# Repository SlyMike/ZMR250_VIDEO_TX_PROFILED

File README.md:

# ZMR250_VIDEO_TX_PROFILED
Video TX for ZMR250 frame with 12x WS2512 LEDs.
Use the board with vertical antenna for best results.

Small switch mode power supplies are available on Ebay, solder directly to under side.
LM1117 3V3 linear regulater may be used for low power applications but not recomended (25mW).
Solder bridge jumper is provided for powering TX on 5V where possible.
Place jumper across 3V3OUT and ENABLE to turn on TX module.

I hope you find this project helpful, maybe it's worth a coffee?

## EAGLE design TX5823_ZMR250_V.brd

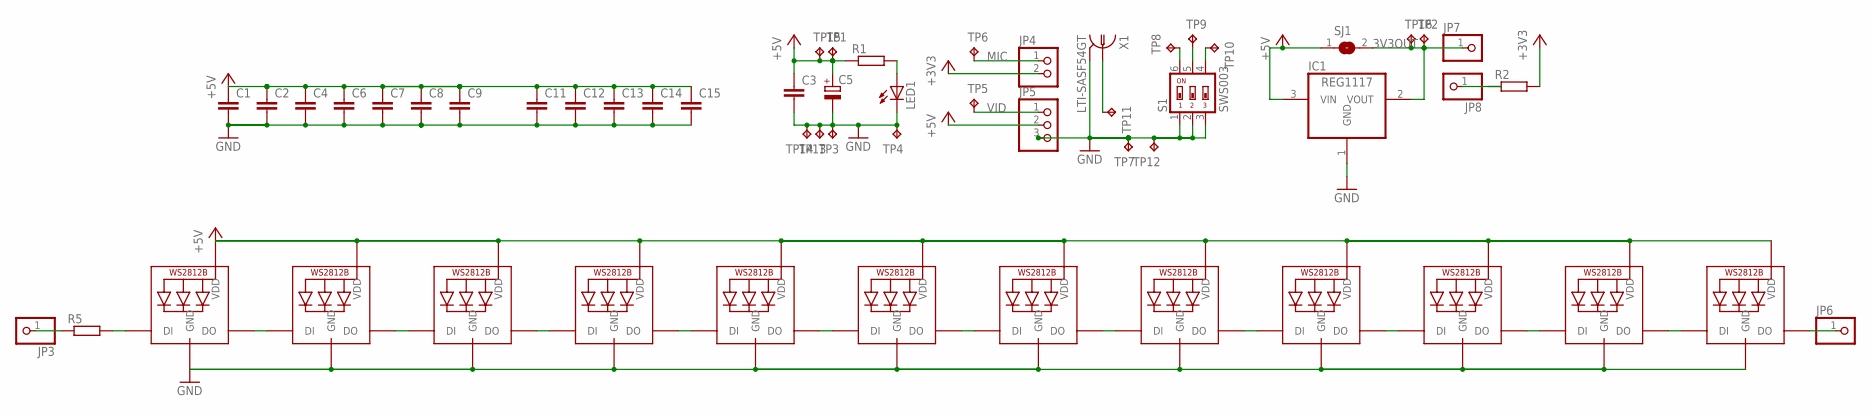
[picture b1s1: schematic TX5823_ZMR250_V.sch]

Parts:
C1, C2, C4, C6, C7, C8, C11, C12: C-EUC0603; C0603
C3, C9, C13, C14, C15: C-EUC0805; C0805
C5: CPOL-EUSMCB; SMC_B
IC1: REG1117; SOT223
JP3, JP6, JP7, JP8: PINHD-1X1; 1X01
JP4: PINHD-1X2; 1X02
JP5: PINHD-1X3; 1X03
LED1: LEDCHIPLED_0603; CHIPLED_0603
LED2, LED3, LED4, LED5, LED6, LED7, LED8, LED9, LED10, LED11, LED12, LED13: WS2812B5050; WS2812B
R1, R5: R-EU_R0603; R0603
R2: R-EU_M1406; M1406
S1: SWS003; SMS-003
SJ1: SJ
TP1, TP2, TP3, TP4, TP5, TP6, TP7, TP8, TP9, TP10, TP11, TP12, TP13, TP14, TP15, TP16: TPB1,27; B1,27
X1: LTI-SASF54GT

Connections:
3V3OUT: IC1.2 (VOUT), JP7.1, SJ1.2, TP2.TP, TP16.TP
+3V3: JP4.2, R2.2
+5V: C1.1, C2.1, C3.1, C4.1, C5.+, C6.1, C7.1, C8.1, C9.1, C11.1, C12.1, C13.1, C14.1, C15.1, IC1.3 (VIN), JP5.2, LED2.1-VDD (VDD), LED3.1-VDD (VDD), LED4.1-VDD (VDD), LED5.1-VDD (VDD), LED6.1-VDD (VDD), LED7.1-VDD (VDD), LED8.1-VDD (VDD), LED9.1-VDD (VDD), LED10.1-VDD (VDD), LED11.1-VDD (VDD), LED12.1-VDD (VDD), LED13.1-VDD (VDD), R1.1, SJ1.1, TP1.TP, TP15.TP
GND: C1.2, C2.2, C3.2, C4.2, C5.-, C6.2, C7.2, C8.2, C9.2, C11.2, C12.2, C13.2, C14.2, C15.2, IC1.1 (GND), JP5.3, LED1.C, LED2.3-GND (GND), LED3.3-GND (GND), LED4.3-GND (GND), LED5.3-GND (GND), LED6.3-GND (GND), LED7.3-GND (GND), LED8.3-GND (GND), LED9.3-GND (GND), LED10.3-GND (GND), LED11.3-GND (GND), LED12.3-GND (GND), LED13.3-GND (GND), S1.1, S1.2, S1.3, TP3.TP, TP4.TP, TP7.TP, TP12.TP, TP13.TP, TP14.TP, X1.2, X1.3 (2), X1.4 (2), X1.5 (2)
IN: LED2.4-DIN (DI), R5.2
IO1: LED2.2-DOUT (DO), LED3.4-DIN (DI)
IO3: LED4.2-DOUT (DO), LED5.4-DIN (DI)
LED_IN: JP3.1, R5.1
MIC: JP4.1, TP6.TP
unnamed: S1.6, TP8.TP
unnamed: S1.5, TP9.TP
unnamed: S1.4, TP10.TP
unnamed: JP8.1, R2.1
unnamed: LED5.2-DOUT (DO), LED6.4-DIN (DI)
unnamed: TP11.TP, X1.1
unnamed: LED8.4-DIN (DI), LED10.2-DOUT (DO)
unnamed: LED3.2-DOUT (DO), LED4.4-DIN (DI)
unnamed: LED1.A, R1.2
unnamed: LED6.2-DOUT (DO), LED7.4-DIN (DI)
unnamed: LED8.2-DOUT (DO), LED11.4-DIN (DI)
unnamed: LED7.2-DOUT (DO), LED9.4-DIN (DI)
unnamed: LED9.2-DOUT (DO), LED10.4-DIN (DI)
unnamed: LED11.2-DOUT (DO), LED12.4-DIN (DI)
unnamed: LED12.2-DOUT (DO), LED13.4-DIN (DI)
unnamed: JP6.1, LED13.2-DOUT (DO)
VID: JP5.1, TP5.TP

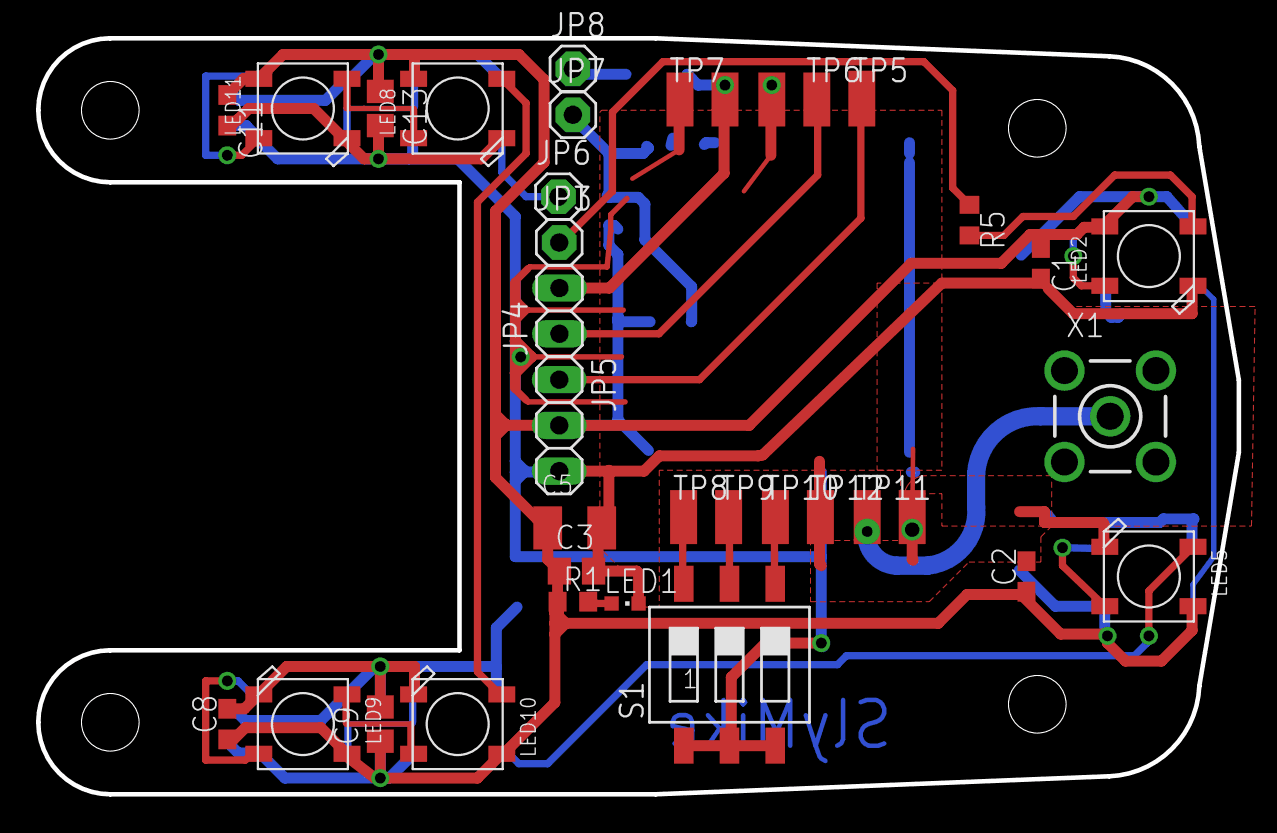
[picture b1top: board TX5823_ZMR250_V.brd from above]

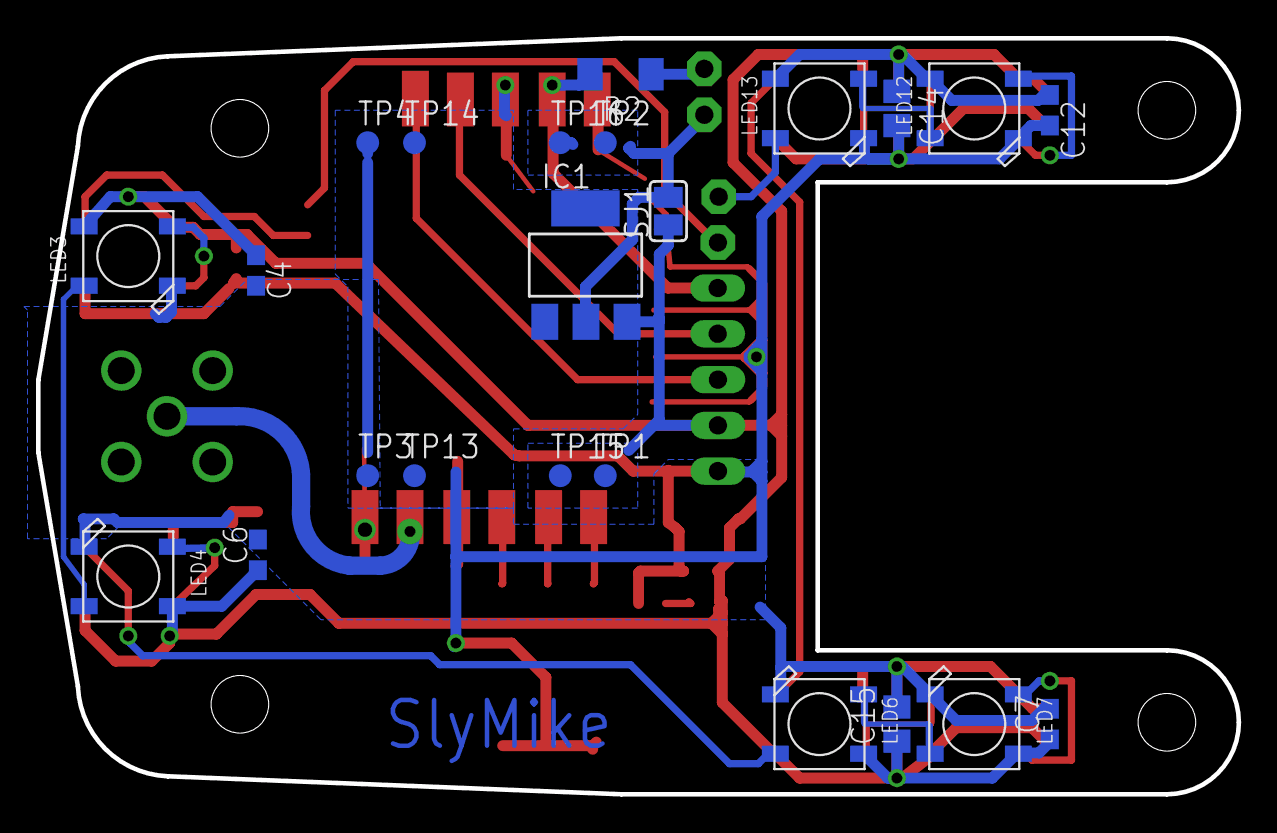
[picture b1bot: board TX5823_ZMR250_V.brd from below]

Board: 2 copper layers, 66.7 x 42.0 mm, 56 parts (23 on the bottom side), 26 nets.

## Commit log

2016-12-01 Add files via upload
    Moved a few parts, changed some via sizes, deleted a capacitor and added more test points for switch mode PSU.
